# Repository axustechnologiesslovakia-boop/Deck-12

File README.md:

# Deck-12
### axustechnologiesslovakia-boop

Deck-12 is a high-performance, 12-key mechanical macro interface featuring integrated OLED telemetry. The project focuses on a compact, ergonomic form factor for streamlined media and system control.

---

## Hardware Specifications

- **Controller**: Seeed Studio Xiao RP2040 (Dual-core ARM Cortex M0+)
- **Display**: 0.91" I2C OLED (128x32 resolution)
- **Input**: 12x Mechanical switches in a 4x3 matrix configuration
- **Connectivity**: USB-C high-speed serial interface
- **Logic Level**: 3.3V native

## Project Structure

- **Firmware/**: C++ source code optimized for the RP2040. Implements debounced switch polling and an I2C buffer for real-time display updates.
- **CAD/**: Parametric design files for the chassis. Optimized for tight tolerances, hardware clearance, and structural rigidity.
- **Case/**: Manufacturing documentation, including a standardized Bill of Materials (BOM) and assembly schematics.

## Engineering Details

### Firmware Logic
The firmware utilizes a non-blocking polling architecture to ensure low-latency input detection. The OLED display is updated via the I2C bus only when a state change is detected to reduce CPU overhead and minimize electromagnetic interference.

### Mechanical Design
The CAD files provide a precision-engineered enclosure designed to house the Xiao RP2040 and the OLED module securely. The design features:
- Integrated mounting points for the RP2040.
- Flush-mount window for the 0.91" OLED.
- Internal cable management channels.

## Bill of Materials (BOM) Summary

| Component | Description | Quantity |
| :--- | :--- | :--- |
| Xiao RP2040 | Main Microcontroller | 1 |
| 0.91" OLED | I2C Display Module | 1 |
| Mechanical Switches | Gateron/Cherry Compatible | 12 |
| Custom Chassis | 3D Printed / CNC Machined | 1 |
| 1N4148 | Signal Diodes (Matrix) | 12 |

## License

Distributed under the MIT License. See `LICENSE` for more information.

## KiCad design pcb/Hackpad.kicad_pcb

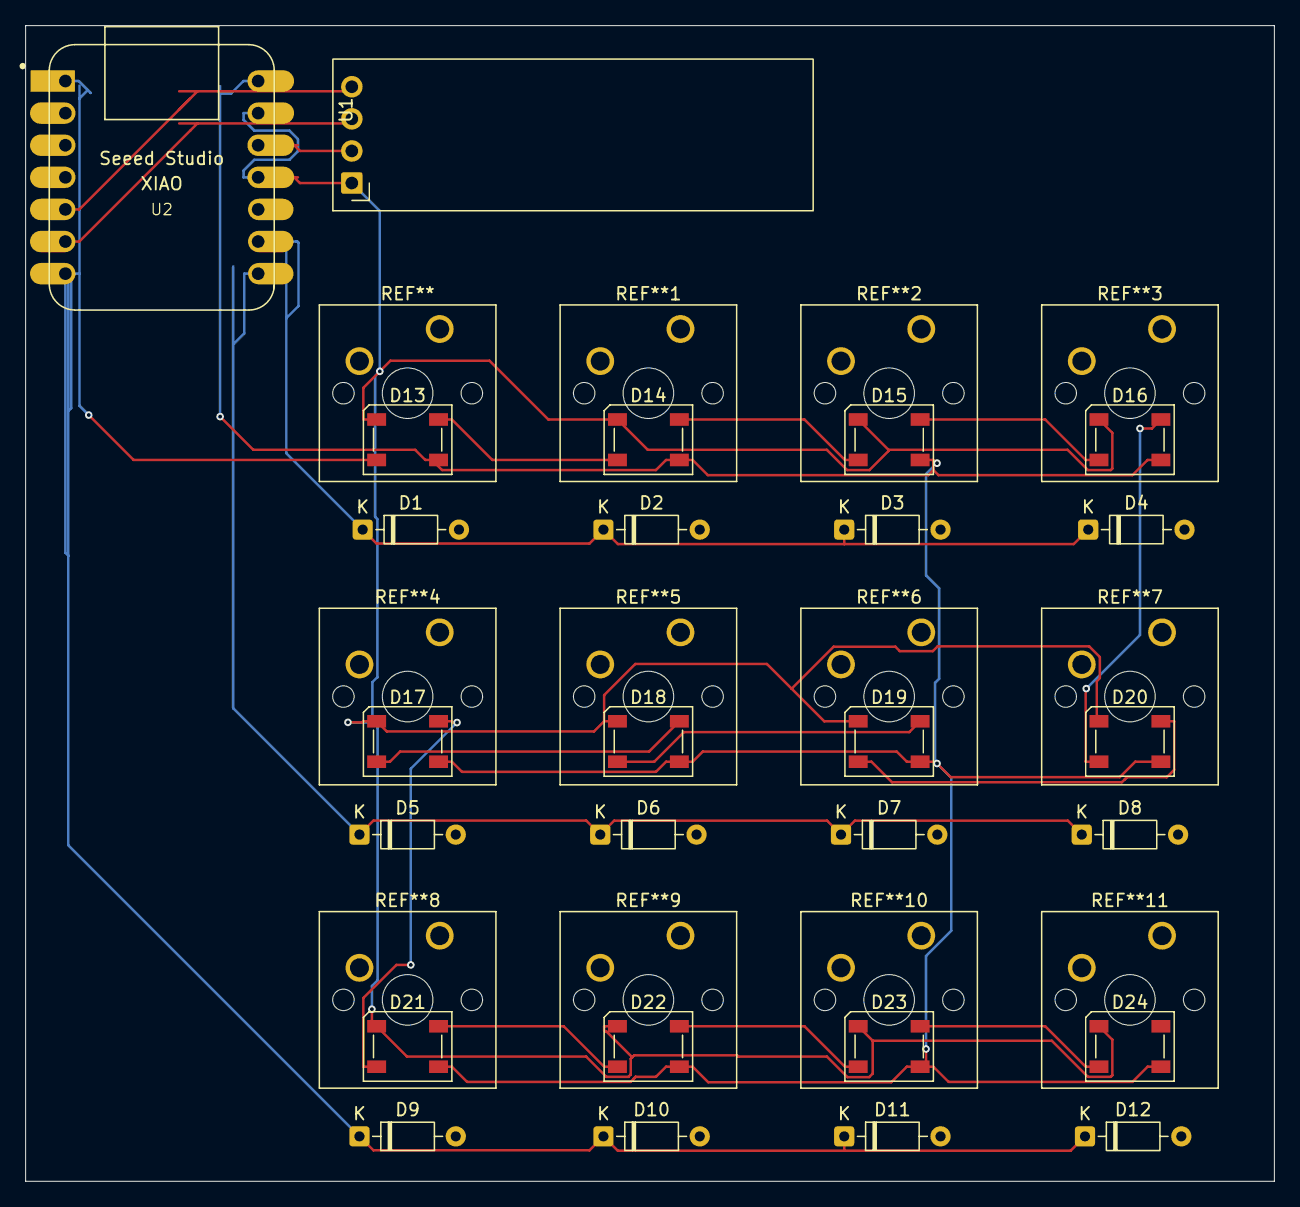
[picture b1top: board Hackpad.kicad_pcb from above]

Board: 2 copper layers, 98.8 x 91.4 mm, 26 parts (0 on the bottom side), 20 nets.

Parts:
D1, D2, D3, D4, D5, D6, D7, D8, D9, D10, D11, D12: 1N4148; D_DO-35_SOD27_P7.62mm_Horizontal
D13, D14, D15, D16, D17, D18, D19, D20, D21, D22, D23, D24: SK6812; LED_SK6812_PLCC4_5.0x5.0mm_P3.2mm
U1: ER_OLEDM0.91_1x-I2C
U2: XIAO-RP2040-DIP; XIAO-Generic-Hybrid-14P-2.54-21X17.8MM

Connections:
unnamed: D1.1 (K), D2.1 (K), D3.1 (K), D4.1 (K), U2.9 (P2_D8_SCK)
unnamed: D5.1 (K), D6.1 (K), D7.1 (K), D8.1 (K), U2.8 (P1_D7_RX)
unnamed: D9.1 (K), D10.1 (K), D11.1 (K), D12.1 (K), U2.7 (P0_D6_TX)
unnamed: D13.2 (DIN), U2.1 (P26_A0_D0)
unnamed: D13.4 (DOUT), D14.2 (DIN)
unnamed: D13.3 (VDD), D14.3 (VDD), D15.3 (VDD), D16.3 (VDD), D17.3 (VDD), D18.3 (VDD), D19.3 (VDD), D20.3 (VDD), D21.3 (VDD), D22.3 (VDD), D23.3 (VDD), D24.3 (VDD), U2.14 (VBUS)
unnamed: D13.1 (VSS), D14.1 (VSS), D15.1 (VSS), D16.1 (VSS), D17.1 (VSS), D18.1 (VSS), D19.1 (VSS), D20.1 (VSS), D21.1 (VSS), D22.1 (VSS), D23.1 (VSS), D24.1 (VSS), U1.1 (GND), U2.11 (P3_D10_MOSI), U2.13 (GND)
unnamed: D14.4 (DOUT), D15.2 (DIN)
unnamed: D15.4 (DOUT), D16.2 (DIN)
unnamed: D16.4 (DOUT), D20.2 (DIN)
unnamed: D17.2 (DIN), D18.4 (DOUT)
unnamed: D17.4 (DOUT), D21.2 (DIN)
unnamed: D18.2 (DIN), D19.4 (DOUT)
unnamed: D19.2 (DIN), D20.4 (DOUT)
unnamed: D21.4 (DOUT), D22.2 (DIN)
unnamed: D22.4 (DOUT), D23.2 (DIN)
unnamed: D23.4 (DOUT), D24.2 (DIN)
unnamed: U1.3 (SCL), U2.6 (P7_SCL_D5)
unnamed: U1.4 (SDA), U2.5 (P6_SDA_D4)
unnamed: U1.2 (VCC), U2.12 (3V3)
